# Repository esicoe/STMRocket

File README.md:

# STMRocket (KiCad v9.0)

> An open source model rocket flight computer with datalogging & parachute deploying capabilities.
> 
<br>

**This project was sponsored and made possible by PCBWay**

<br>

## Project Description

This is a personal project for an STM32 flight computer that will be flown on a high-power rocket to achieve the Level 1 high power rocketry certification in Canada.
<br>

## Capabilities

The computer is able to store flight data from its two sensors:

- ICM42670: 6-axis IMU with a gyroscope and accelerometer
- BME280: Pressure, temperature and humidity sensor

Data from the accelerometer and gyroscope is used to activate the pyro charge and release the rocket's parachute (single-deploy configuration).

Flight data is stored in a 4-megabyte flash memory chip and is offloaded from the computer using MicroSD.
<br>

During flight, the computer is powered by a 2S LiPo battery through an XT30 connector.

Programming interfaces: SWD and USB Micro-B.

<br>

For a more detailed overview of the components, consult the BOM and the KiCad schematic.

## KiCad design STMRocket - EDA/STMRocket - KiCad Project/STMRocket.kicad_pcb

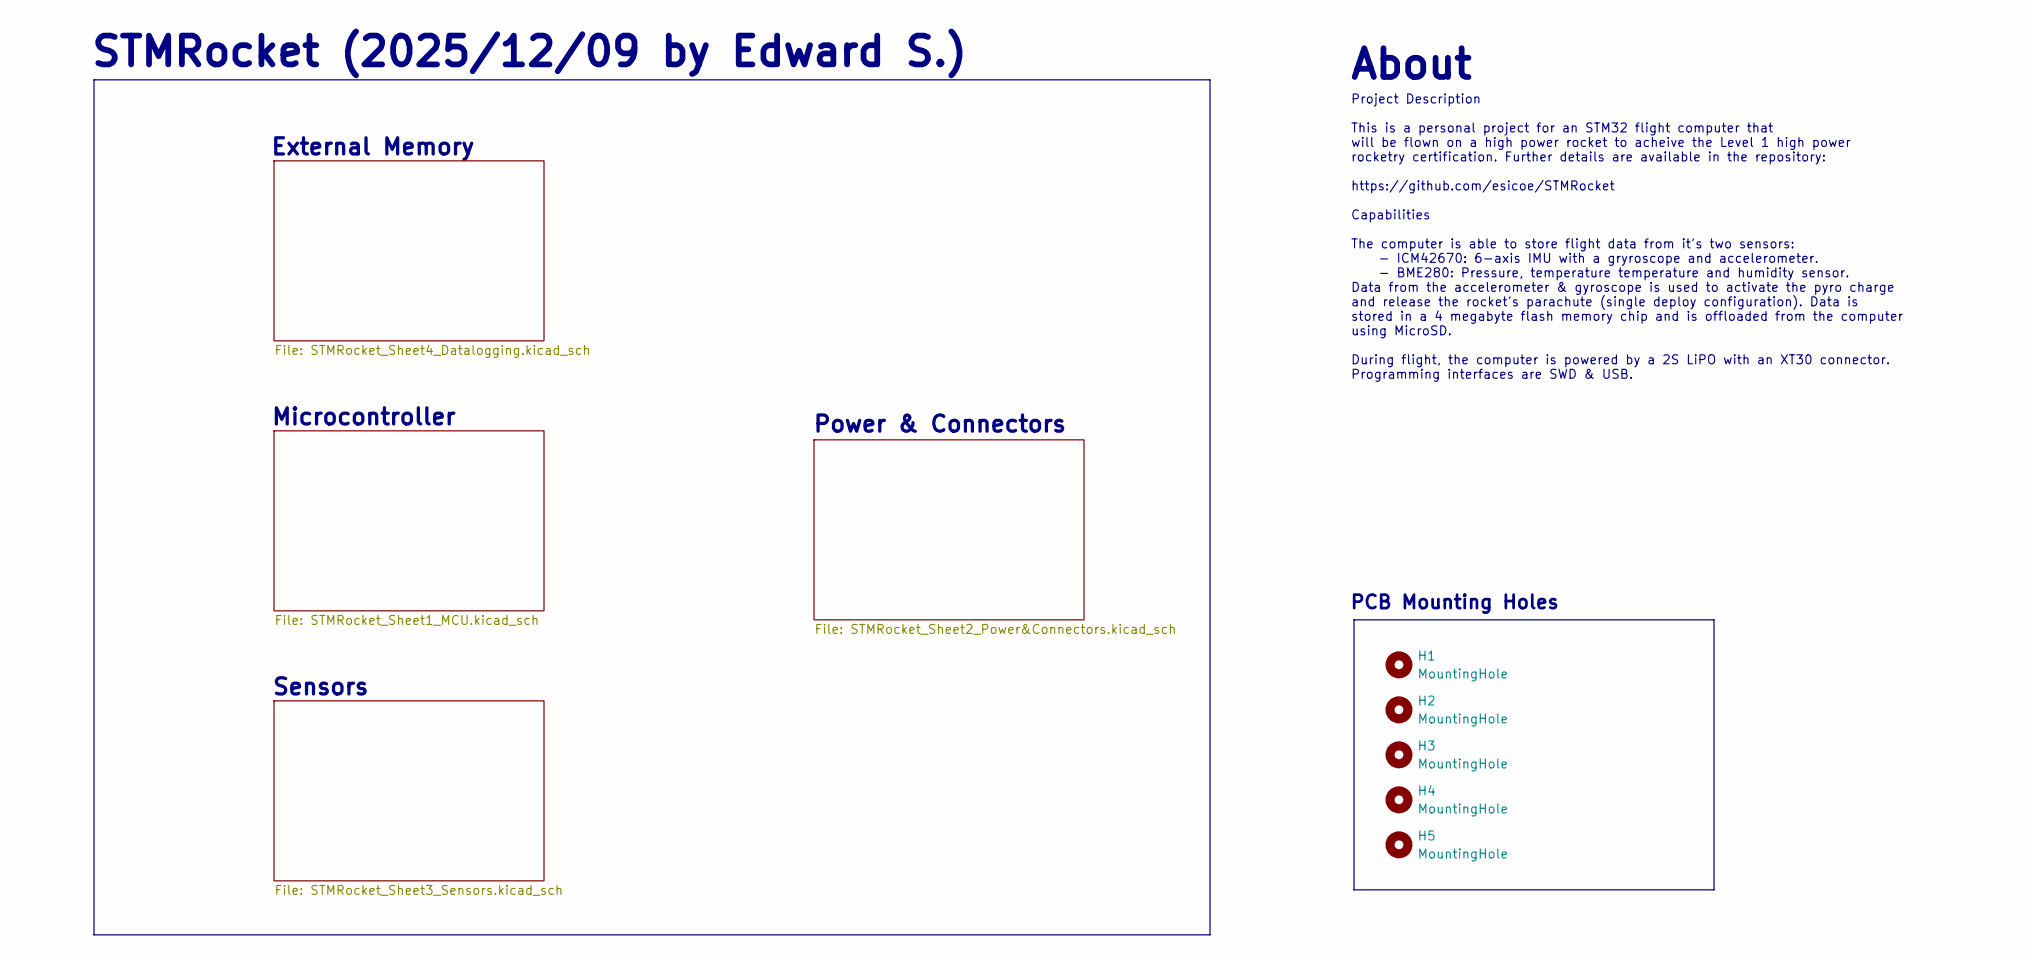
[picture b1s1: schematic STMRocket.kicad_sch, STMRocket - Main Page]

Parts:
H1, H2, H3, H4, H5: MountingHole; MountingHole_2.2mm_M2

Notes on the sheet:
PCB Mounting Holes
STMRocket (2025/12/09 by Edward S.)
Project Description This is a personal project for an STM32 flight computer that will be flown on a high power rocket to acheive the Level 1 high power rocketry certification. Further details are available in the repository: https://github.com/esicoe/STMRocket Capabilities The computer is able to s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
About
Sensors
External Memory
Microcontroller
Power & Connectors

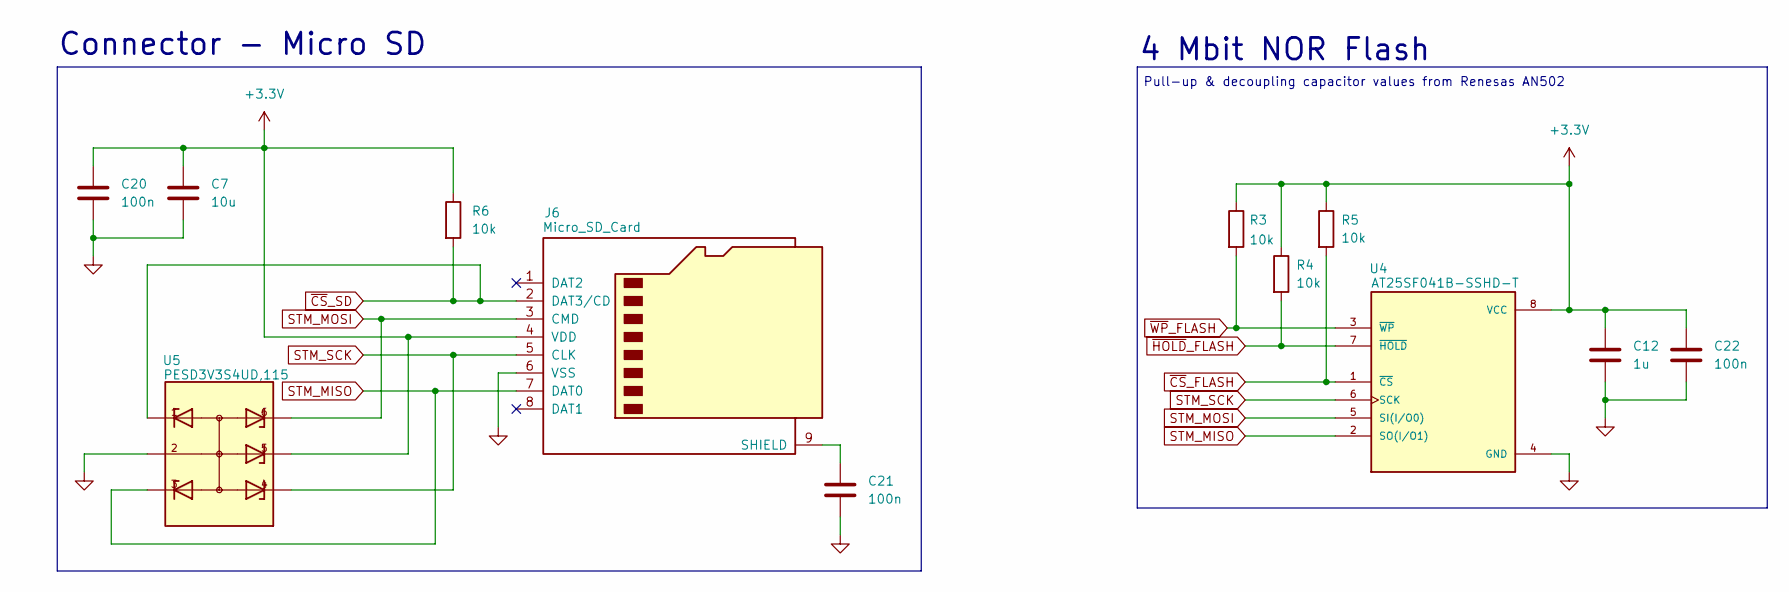
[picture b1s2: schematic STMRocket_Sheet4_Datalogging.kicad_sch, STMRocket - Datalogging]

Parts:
C7: 10u; C_0603_1608Metric
C12: 1u; C_0402_1005Metric
C20, C21, C22: 100n; C_0402_1005Metric
J6: Micro_SD_Card; microSD_HC_Wuerth_693072010801
R3, R4, R5, R6: 10k; R_0402_1005Metric
U4: AT25SF041B-SSHD-T; SOIC-8_3.9x4.9mm_P1.27mm; PARTREV G
U5: PESD3V3S4UD,115; SC-74-6_1.55x2.9mm_P0.95mm

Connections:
+3.3V: C7.1, C12.1, C20.1, C22.1, J6.4 (VDD), R3.1, R4.1, R5.1, R6.1, U4.8 (VCC), U5.5; also elsewhere on the board
unnamed: C21.1, J6.9 (SHIELD)
STM_MISO: J6.7 (DAT0), U4.2 (SO(I/O1)), U5.3; also elsewhere on the board
STM_MOSI: J6.3 (CMD), U4.5 (SI(I/O0)), U5.6; also elsewhere on the board
STM_SCK: J6.5 (CLK), U4.6 (SCK), U5.4; also elsewhere on the board
~CS_FLASH: R5.2, U4.1 (~CS); also elsewhere on the board
~CS_SD: J6.2 (DAT3/CD), R6.2, U5.1; also elsewhere on the board
~HOLD_FLASH: R4.2, U4.7 (~HOLD); also elsewhere on the board
~WP_FLASH: R3.2, U4.3 (~WP); also elsewhere on the board

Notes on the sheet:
Pull-up & decoupling capacitor values from Renesas AN502
4 Mbit NOR Flash
Connector - Micro SD

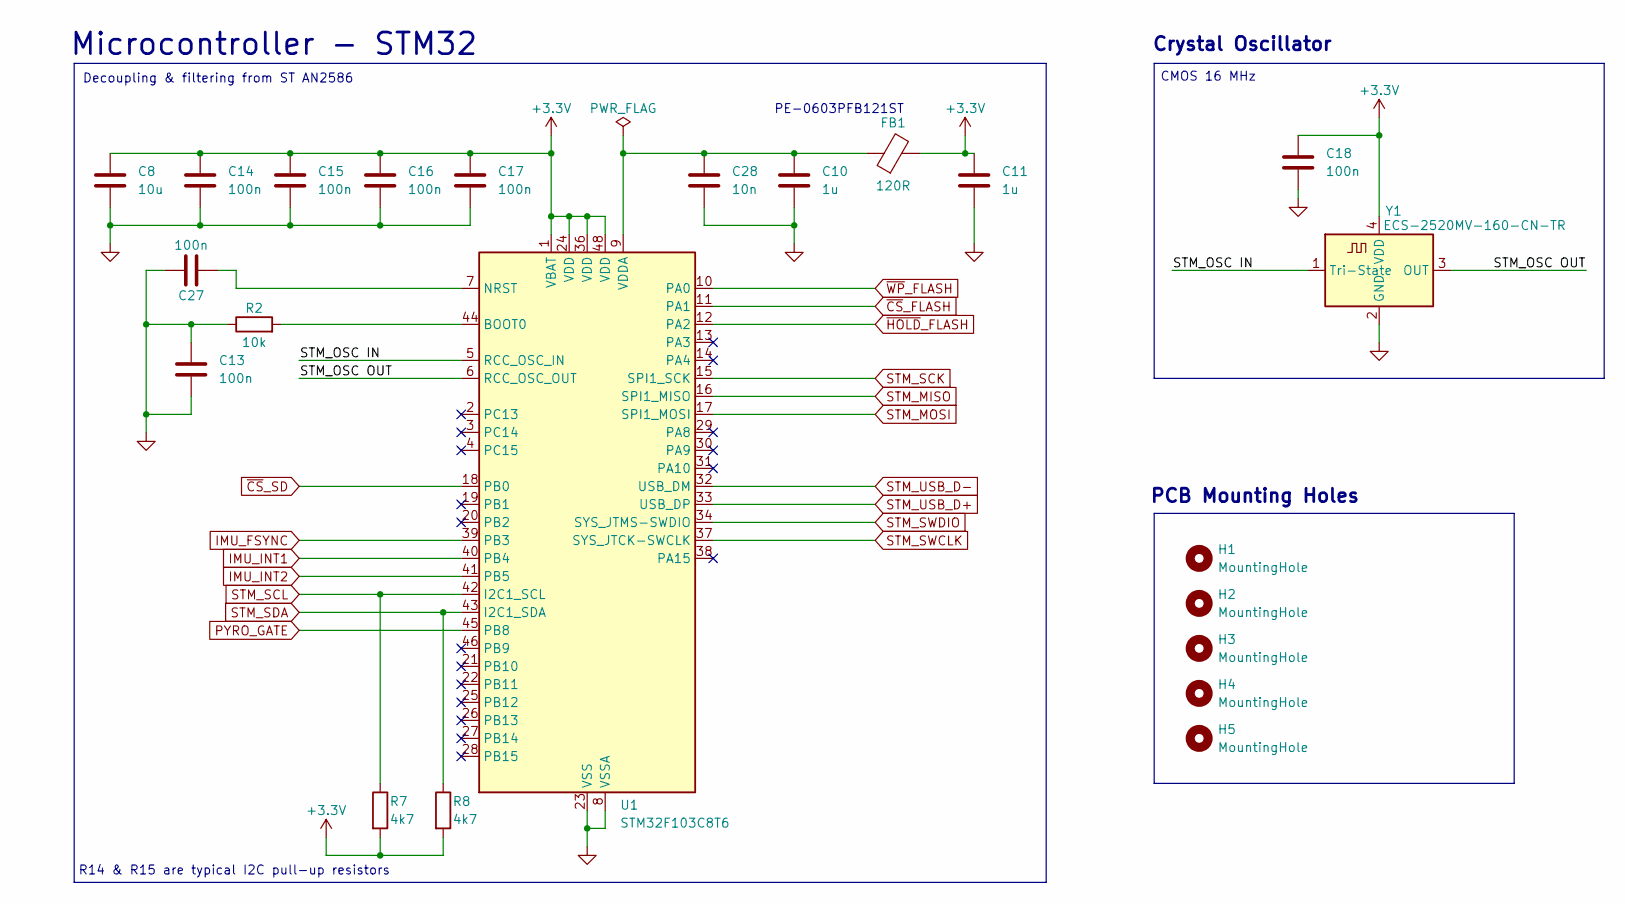
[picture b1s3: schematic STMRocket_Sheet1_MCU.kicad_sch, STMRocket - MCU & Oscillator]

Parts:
C8: 10u; C_0603_1608Metric
C10, C11: 1u; C_0402_1005Metric
C13, C14, C15, C16, C17, C18, C27: 100n; C_0402_1005Metric
C28: 10n; C_0402_1005Metric
FB1: 120R; L_0603_1608Metric
H1, H2, H3, H4, H5: MountingHole; MountingHole_2.2mm_M2
R2: 10k; R_0402_1005Metric
R7, R8: 4k7; R_0402_1005Metric
U1: STM32F103C8T6; LQFP-48_7x7mm_P0.5mm
Y1: ECS-2520MV-160-CN-TR; Oscillator_SMD_ECS_2520MV-xxx-xx-4Pin_2.5x2.0mm

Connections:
+3.3V: C8.1, C11.1, C14.1, C15.1, C16.1, C17.1, C18.1, FB1.2, R7.2, R8.2, U1.1 (VBAT), U1.24 (VDD), U1.36 (VDD), U1.48 (VDD), Y1.4 (VDD); also elsewhere on the board
/MCU/STM_OSC IN: U1.5 (RCC_OSC_IN), Y1.1 (Tri-State)
/MCU/STM_OSC OUT: U1.6 (RCC_OSC_OUT), Y1.3 (OUT)
IMU_FSYNC: U1.40 (PB4); also elsewhere on the board
IMU_INT1: U1.41 (PB5); also elsewhere on the board
IMU_INT2: U1.39 (PB3); also elsewhere on the board
unnamed: C27.2, U1.7 (NRST)
unnamed: C10.1, C28.1, FB1.1, U1.9 (VDDA)
PYRO_GATE: U1.45 (PB8); also elsewhere on the board
STM_MISO: U1.16 (SPI1_MISO); also elsewhere on the board
STM_MOSI: U1.17 (SPI1_MOSI); also elsewhere on the board
STM_SCK: U1.15 (SPI1_SCK); also elsewhere on the board
STM_SCL: R7.1, U1.42 (I2C1_SCL); also elsewhere on the board
STM_SDA: R8.1, U1.43 (I2C1_SDA); also elsewhere on the board
STM_SWCLK: U1.37 (SYS_JTCK-SWCLK); also elsewhere on the board
STM_SWDIO: U1.34 (SYS_JTMS-SWDIO); also elsewhere on the board
STM_USB_D+: U1.33 (USB_DP); also elsewhere on the board
STM_USB_D-: U1.32 (USB_DM); also elsewhere on the board
~CS_FLASH: U1.11 (PA1); also elsewhere on the board
~CS_SD: U1.18 (PB0); also elsewhere on the board
~HOLD_FLASH: U1.12 (PA2); also elsewhere on the board
~WP_FLASH: U1.10 (PA0); also elsewhere on the board

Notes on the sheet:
Decoupling & filtering from ST AN2586
CMOS 16 MHz
PE-0603PFB121ST
R14 & R15 are typical I2C pull-up resistors
Microcontroller - STM32
Crystal Oscillator
PCB Mounting Holes

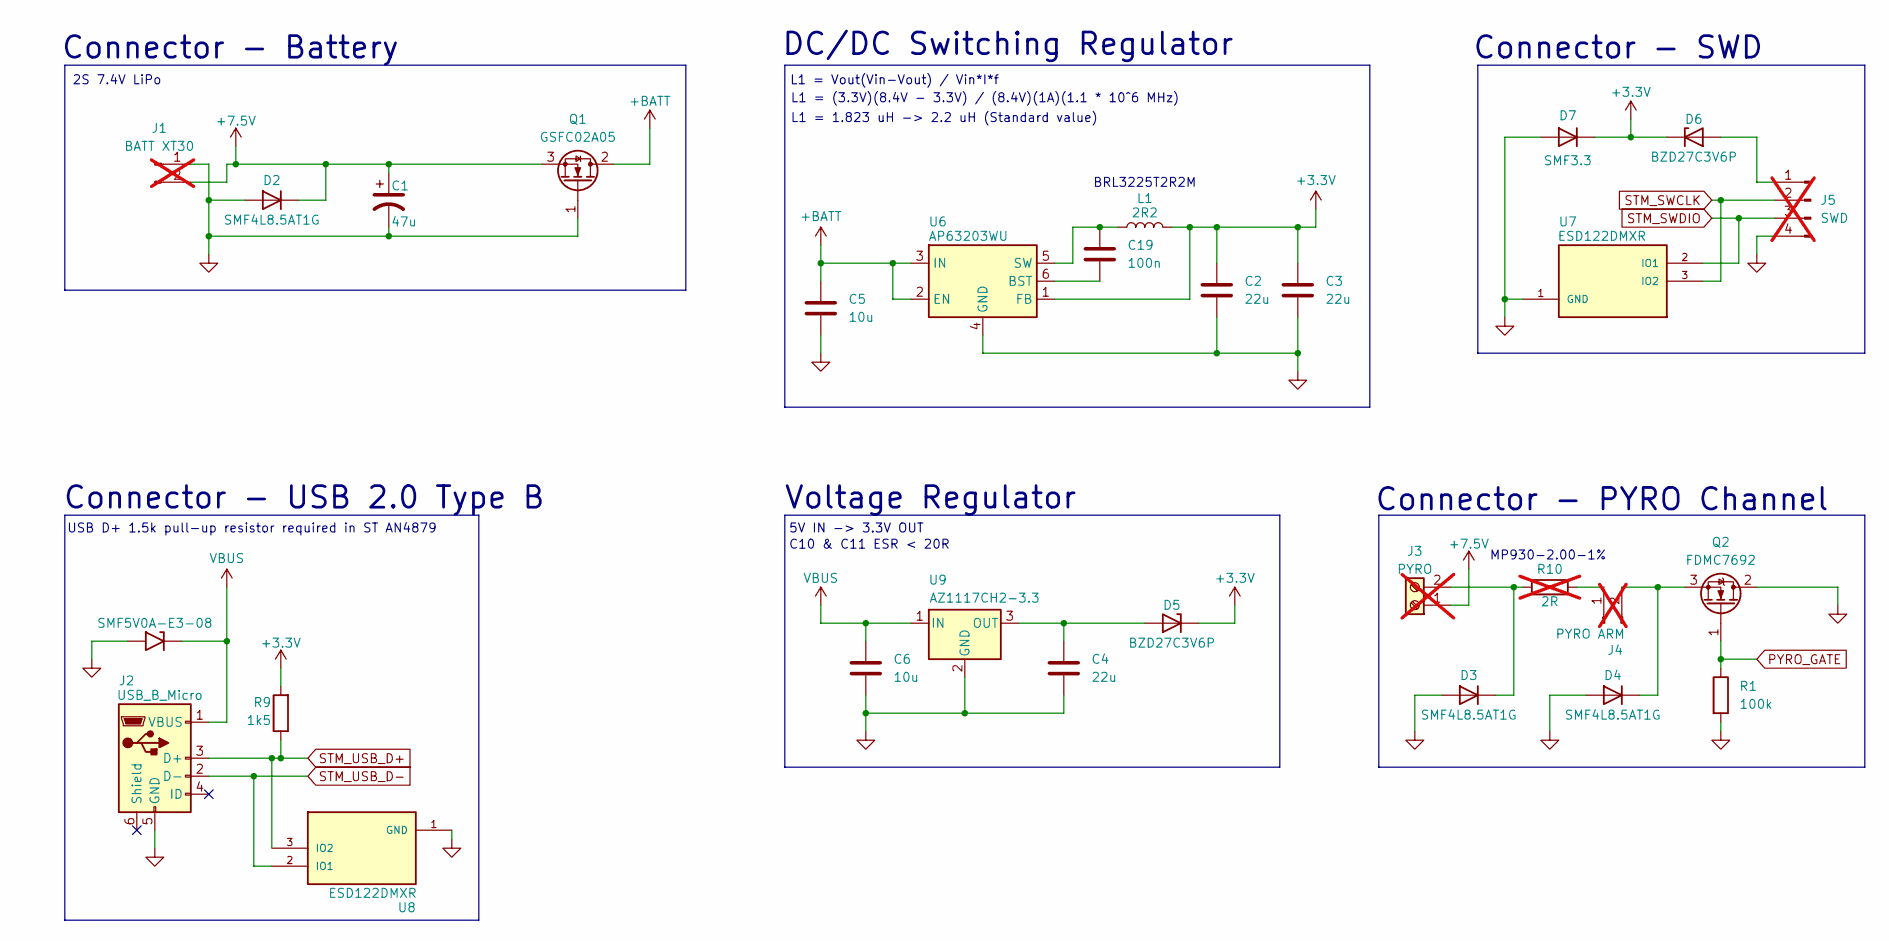
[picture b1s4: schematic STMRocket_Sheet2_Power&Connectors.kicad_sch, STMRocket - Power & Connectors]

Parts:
C1: 47u; CP_Elec_6.3x5.2
C2, C3, C4: 22u; C_0805_2012Metric
C5, C6: 10u; C_0603_1608Metric
C19: 100n; C_0402_1005Metric
D1: SMF5V0A-E3-08; D_SMF
D2, D3, D4: SMF4L8.5AT1G; D_SOD-123F
D5, D6: BZD27C3V6P; D_SMF
D7: SMF3.3; D_SOD-123F
J1: BATT XT30; AMASS_XT30PW-M_1x02_P2.50mm_Horizontal; not fitted
J2: USB_B_Micro; USB_Micro-B_Amphenol_10103594-0001LF_Horizontal
J3: PYRO; TerminalBlock_RND_205-00001_1x02_P5.00mm_Horizontal; not fitted
J4: PYRO ARM; PinHeader_1x02_P2.54mm_Vertical; not fitted
J5: SWD; PinHeader_1x04_P2.54mm_Vertical; not fitted
L1: 2R2; L_1210_3225Metric
Q1: GSFC02A05; SOT-23-3
Q2: FDMC7692; TO-252-2
R1: 100k; R_0402_1005Metric
R9: 1k5; R_0402_1005Metric
R10: 2R; TO-220-2_Horizontal_TabDown; not fitted
U6: AP63203WU; TSOT-23-6
U7, U8: ESD122DMXR; IC_ESD122DMXR; PARTREV A
U9: AZ1117CH2-3.3; SOT-223-3_TabPin2

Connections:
+3.3V: C2.1, C3.1, D5.1 (K), D6.1 (K), D7.1 (K), L1.2, R9.2, U6.1 (FB); also elsewhere on the board
+7.5V: C1.1, D2.1 (K), J1.2, J3.1, Q1.3 (S)
+BATT: C5.1, Q1.2 (D), U6.2 (EN), U6.3 (IN)
unnamed: D3.1 (K), J3.2, R10.2
unnamed: D4.1 (K), J4.2, Q2.3 (S)
unnamed: C4.1, D5.2 (A), U9.3 (OUT)
unnamed: D6.2 (A), J5.1
unnamed: J4.1, R10.1
unnamed: C19.2, U6.6 (BST)
unnamed: C19.1, L1.1, U6.5 (SW)
PYRO_GATE: Q2.1 (G), R1.1; also elsewhere on the board
STM_SWCLK: J5.2, U7.3 (IO2); also elsewhere on the board
STM_SWDIO: J5.3, U7.2 (IO1); also elsewhere on the board
STM_USB_D+: J2.3 (D+), R9.1, U8.3 (IO2); also elsewhere on the board
STM_USB_D-: J2.2 (D-), U8.2 (IO1); also elsewhere on the board
VBUS: C6.1, D1.1 (A1), J2.1 (VBUS), U9.1 (IN)

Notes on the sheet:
DC/DC Switching Regulator
Connector - Battery
MP930-2.00-1%
Voltage Regulator
Connector - USB 2.0 Type B
USB D+ 1.5k pull-up resistor required in ST AN4879
5V IN -> 3.3V OUT
L1 = 1.823 uH -> 2.2 uH (Standard value)
L1 = Vout(Vin-Vout) / Vin*I*f
2S 7.4V LiPo
C10 & C11 ESR < 20R
L1 = (3.3V)(8.4V - 3.3V) / (8.4V)(1A)(1.1 * 10^6 MHz)
Connector - PYRO Channel
Connector - SWD
BRL3225T2R2M

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
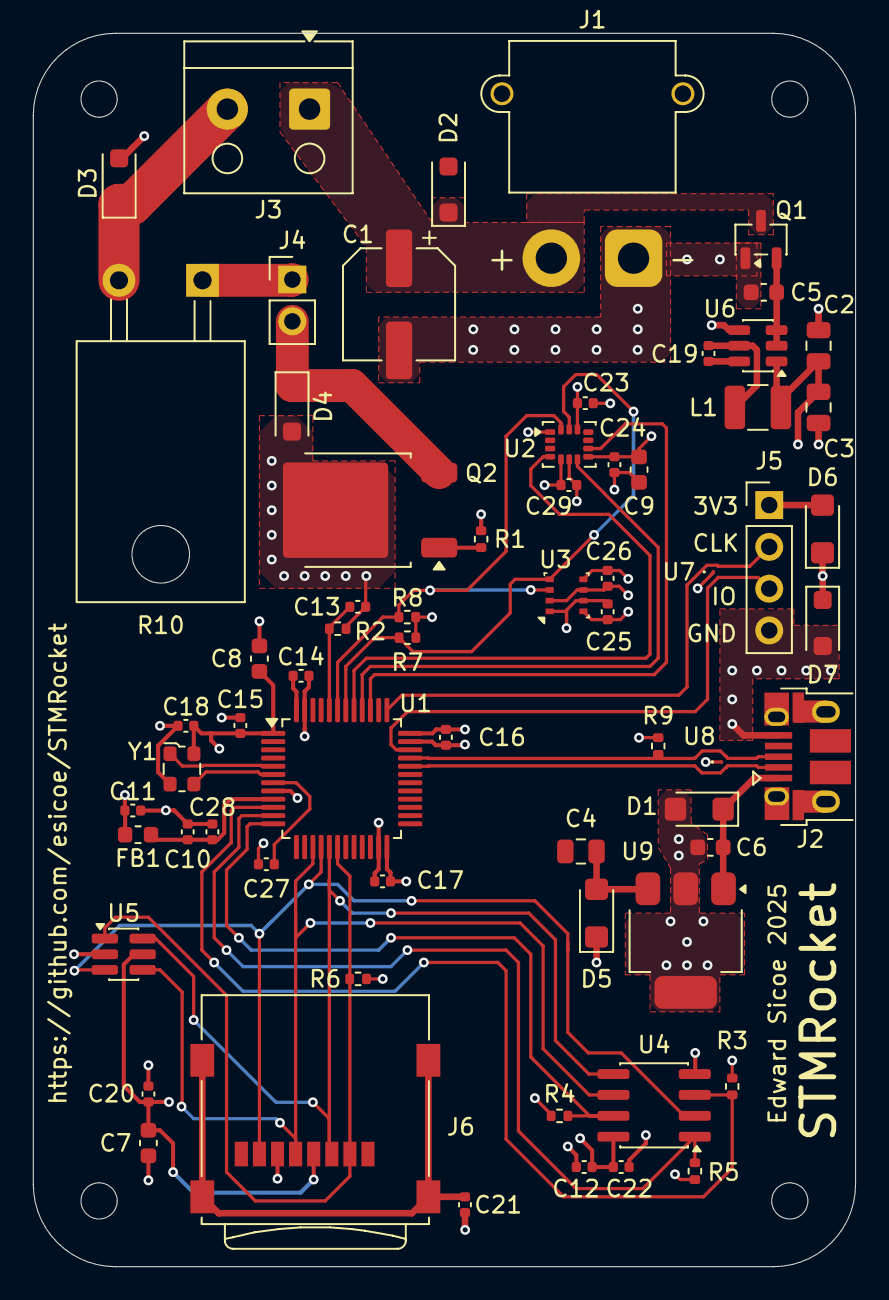
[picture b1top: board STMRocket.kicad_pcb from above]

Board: 4 copper layers, 50.0 x 75.0 mm, 70 parts (0 on the bottom side), 35 nets.

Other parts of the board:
C9: 2.2u; C_0603_1608Metric
C23, C24, C25, C26: 100n; C_0402_1005Metric
C29: 10n; C_0402_1005Metric
U2: ICM-42670-P; LGA-14_3x2.5mm_P0.5mm_LayoutBorder3x4y
U3: BME280; Bosch_LGA-8_2.5x2.5mm_P0.65mm_ClockwisePinNumbering

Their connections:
+3.3V: C9.1, C23.1, C24.1, C25.1, C26.1, C29.1, U2.5 (VDDIO), U2.8 (VDD), U2.12 (AP_CS), U3.2 (CSB), U3.6 (VDDIO), U3.8 (VDD); also elsewhere on the board
IMU_FSYNC: U2.7 (FSYNC); also elsewhere on the board
IMU_INT1: U2.4 (INT1/INT); also elsewhere on the board
IMU_INT2: U2.9 (INT2); also elsewhere on the board
STM_SCL: U2.13 (AP_SCL/AP_SCLK), U3.4 (SCK); also elsewhere on the board
STM_SDA: U2.14 (AP_SDA/AP_SDIO/AP_SDI), U3.3 (SDI); also elsewhere on the board

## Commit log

2025-11-19 2025/11/18
2025-11-20 2025/11/19
2025-11-21 2025/11/21
2025-11-22 2025/11/22
2025-12-10 2025/09/12
2025-12-10 Datasheet renaming and schematic formatting, text, tables, etc.
2025-12-13 Updated layout, documentation and schematic. Component placement finished.
2025-12-14 PCB update
2025-12-15 finished pcb
2025-12-27 pcb update and bom
2025-12-29 PCB finished
2025-12-29 Final PCB revision
2025-12-29 Final - PCB, Man. Files & BOM
2025-12-29 Enhance README with project details and images
    Added project description and images to README.
2025-12-29 Fix README.md by removing duplicate image
    Removed duplicate image tag and adjusted formatting.
2025-12-29 Update project title to include KiCad version
2025-12-29 Improve formatting in README.md
    Added line breaks for better readability in README.
2025-12-31 Add sponsorship note and images to README
    Added sponsorship acknowledgment and images.
2026-01-01 Update manufacturing files
2026-01-01 Clean up README formatting
    Removed unnecessary line breaks in the README.
2026-01-01 v1.0
